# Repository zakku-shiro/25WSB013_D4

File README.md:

# project-pied-piper

This project is for the 25WSB013 - Project Design and Management module at Loughborough University, tackling specifically the "Pied Piper" challenge.

## Useful Links

### [Generic Project Information](https://learn.lboro.ac.uk/mod/forum/discuss.php?d=498549)

### [Pied Piper Specific Information](https://learn.lboro.ac.uk/mod/forum/discuss.php?d=498557)

### [RobotShop Rover Link](https://uk.robotshop.com/products/dfrobotshop-rover-tracked-robot-basic-kit)

### [Markdown Guide](https://www.markdownguide.org/basic-syntax/)

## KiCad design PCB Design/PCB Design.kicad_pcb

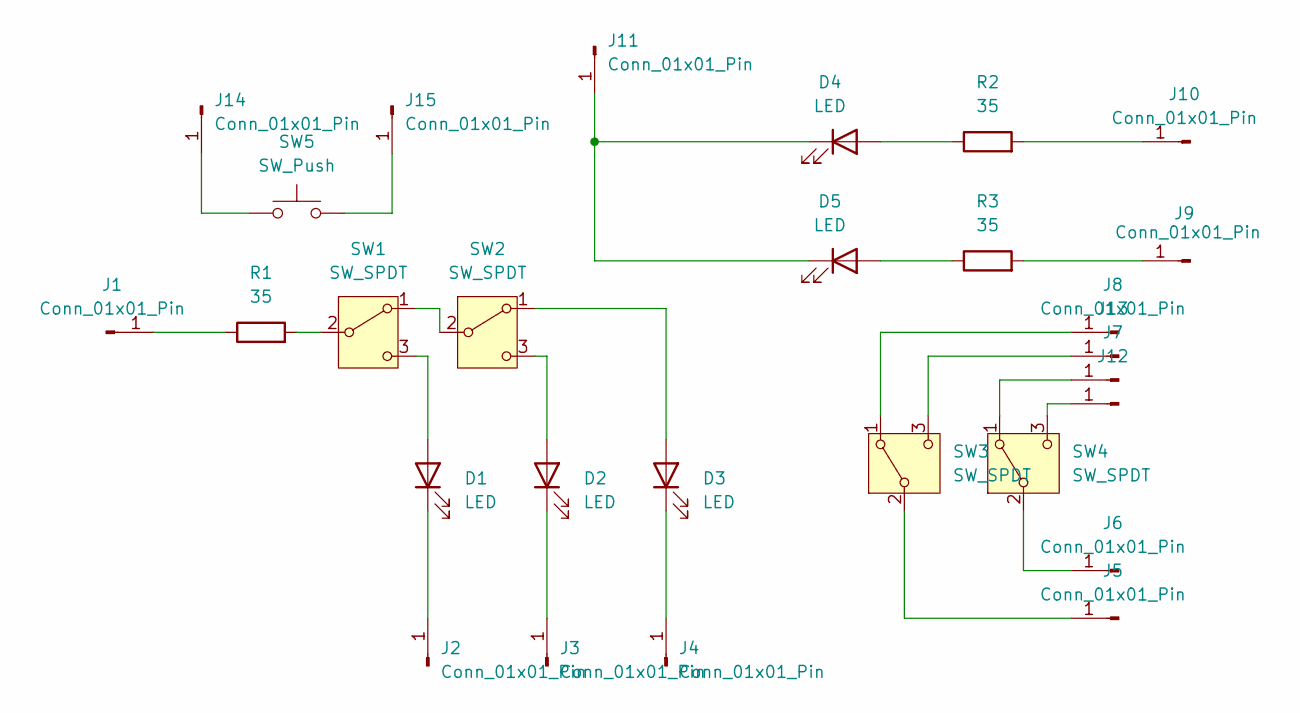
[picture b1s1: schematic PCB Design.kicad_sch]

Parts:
D1, D2, D3, D4, D5: LED; LED_D3.0mm
J1, J2, J3, J4, J5, J6, J7, J8, J9, J10, J11, J12, J13, J14, J15: Conn_01x01_Pin; SolderWire-1sqmm_1x01_D1.4mm_OD2.7mm
R1, R2, R3: 35; R_Axial_DIN0207_L6.3mm_D2.5mm_P10.16mm_Horizontal
SW1, SW2, SW3, SW4: SW_SPDT
SW5: SW_Push

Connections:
unnamed: D1.2 (A), SW1.3 (C)
unnamed: D1.1 (K), J2.1
unnamed: D2.2 (A), SW2.3 (C)
unnamed: D2.1 (K), J3.1
unnamed: D3.2 (A), SW2.1 (A)
unnamed: D3.1 (K), J4.1
unnamed: D4.2 (A), R2.1
unnamed: D4.1 (K), D5.1 (K), J11.1
unnamed: D5.2 (A), R3.1
unnamed: J1.1, R1.1
unnamed: J5.1, SW3.2 (B)
unnamed: J6.1, SW4.2 (B)
unnamed: J7.1, SW4.1 (A)
unnamed: J8.1, SW3.1 (A)
unnamed: J9.1, R3.2
unnamed: J10.1, R2.2
unnamed: J12.1, SW4.3 (C)
unnamed: J13.1, SW3.3 (C)
unnamed: J14.1, SW5.1
unnamed: J15.1, SW5.2
unnamed: SW1.1 (A), SW2.2 (B)
unnamed: R1.2, SW1.2 (B)

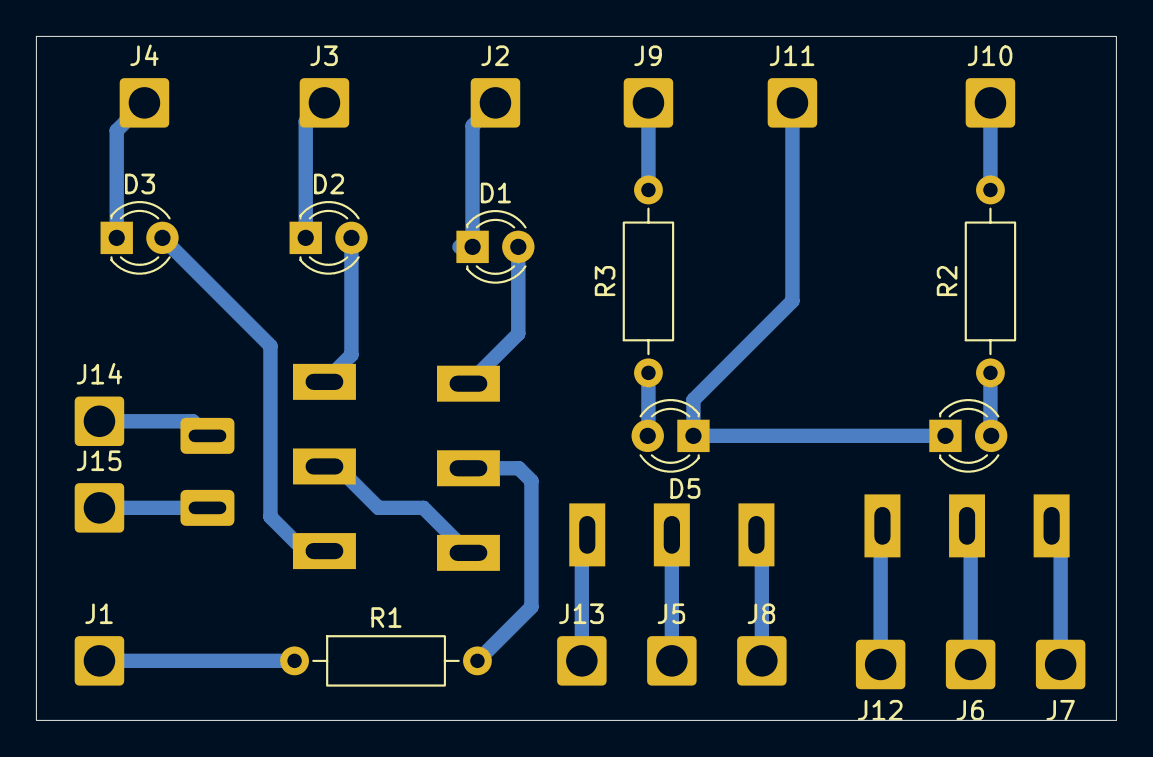
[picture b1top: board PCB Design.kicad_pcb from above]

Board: 2 copper layers, 60.0 x 38.0 mm, 28 parts (0 on the bottom side), 22 nets.

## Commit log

2025-11-05 Add preloaded rover movement code
2025-11-05 Add RobotRover sample code
2025-11-05 Add vscode .clang-format config
2025-11-06 Create Platform IO Project for Arduino
2025-11-06 Update Defines and Add Datasheet
2025-11-14 Initial Commits for PCB
2025-11-15 intial circuit implementation
2025-11-16 adjustements the PCB schematic
2025-11-16 adding contraints
2025-11-16 change in name to link the schematic and pcb platforms
2025-11-16 problem solved
2025-11-16 intial pcb desin and testing of 3d model - some contraint voilations
2025-11-17 Refactor ready for RaspPi code
2025-11-18 edits made to the pcv layout
2025-11-18 altered schematic and PCB layout for new SPDT switches
2025-11-19 demo code of functionality of the ultrasonic sensor with reference to rover behaviour
2025-11-20 Refactor added code's structure
2025-11-20 Set up OpenCV and test smile detection
2025-11-21 adding footprint for the swithces
2025-11-21 completed main pcb design
2025-11-21 edits to design
2025-11-23 added Gerber files
2025-11-23 adding LED testing code to check resistor values
2025-11-23 integration of ultrasonic sensor with movement code
2025-12-03 added sound data collection file to be integrated
2025-12-03 moved to correct location
2025-12-03 made 3d prints folder
2025-12-03 Added files for finished ultrasonic housing
2025-12-05 updated to include bit packing
2025-12-08 added cross correlation file
2025-12-08 Updated sound system, probably works. More comments as well
2025-12-09 alterations to pcb design
2025-12-09 alterations to movement code
2026-02-05 Unify pi and windows version for easier prototyping
2026-02-18 Update .gitignore and transition to dotenv configs.
2026-02-18 Fix unpacking issue and boolean evals
2026-02-18 Add demo bi-directional serial communication code
2026-02-25 adding the USS validation of the location of speaker and light
2026-02-25 changes to the distnace verification code
2026-02-26 New and improved blob detection method (just miles better)
2026-02-26 Update camera exposure settings
2026-03-04 Fix pi-camera auto-exposure and disable auto-white-balance
2026-03-04 additions to make USS sensor code work
2026-03-11 Added all files used for 3d printing(excluding fusion model files not exported)
2026-03-16 Beginnings of integrated communications
2026-03-17 Command line movement control
2026-03-17 Add .env support for serial port
2026-03-17 added double adc prescaler
2026-03-19 added spectra file, sample rate stable, working on correlation more
2026-04-13 improved sound system probably
2026-04-14 has confidence values, >0.15 is good-no background noise considered
2026-04-17 added comments and removed unneccesary bits
2026-04-18 changes to the pcb
2026-04-20 slight tweaks, may be more reliable
2026-04-22 small changes
2026-04-22 Update to current working format of communications & control
2026-04-22 Update to current working format of communications & control - Pi
2026-04-22 Sound system working LED test
2026-04-22 Begin switch status creation
2026-04-22 Working switches and lights
2026-04-22 Hopes and prayers
2026-04-22 Hopes and prayers 2
2026-04-24 Final Working Version
2026-04-24 subsystem-integration (#3)
    * Command line movement control
    * Command line movement control
    * Add .env support for serial port
    * Update to current working format of communications & control
    * Update to current working format of communications & control - Pi
    * Update to current working format of communications & control - Pi
